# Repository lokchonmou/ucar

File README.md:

# ucar
ucar is a Arduino Nano base, PCB integrate,  universal purpose robot car 
This repository include PCB eagle circuit and an I2C LCD user interface firmware for line following

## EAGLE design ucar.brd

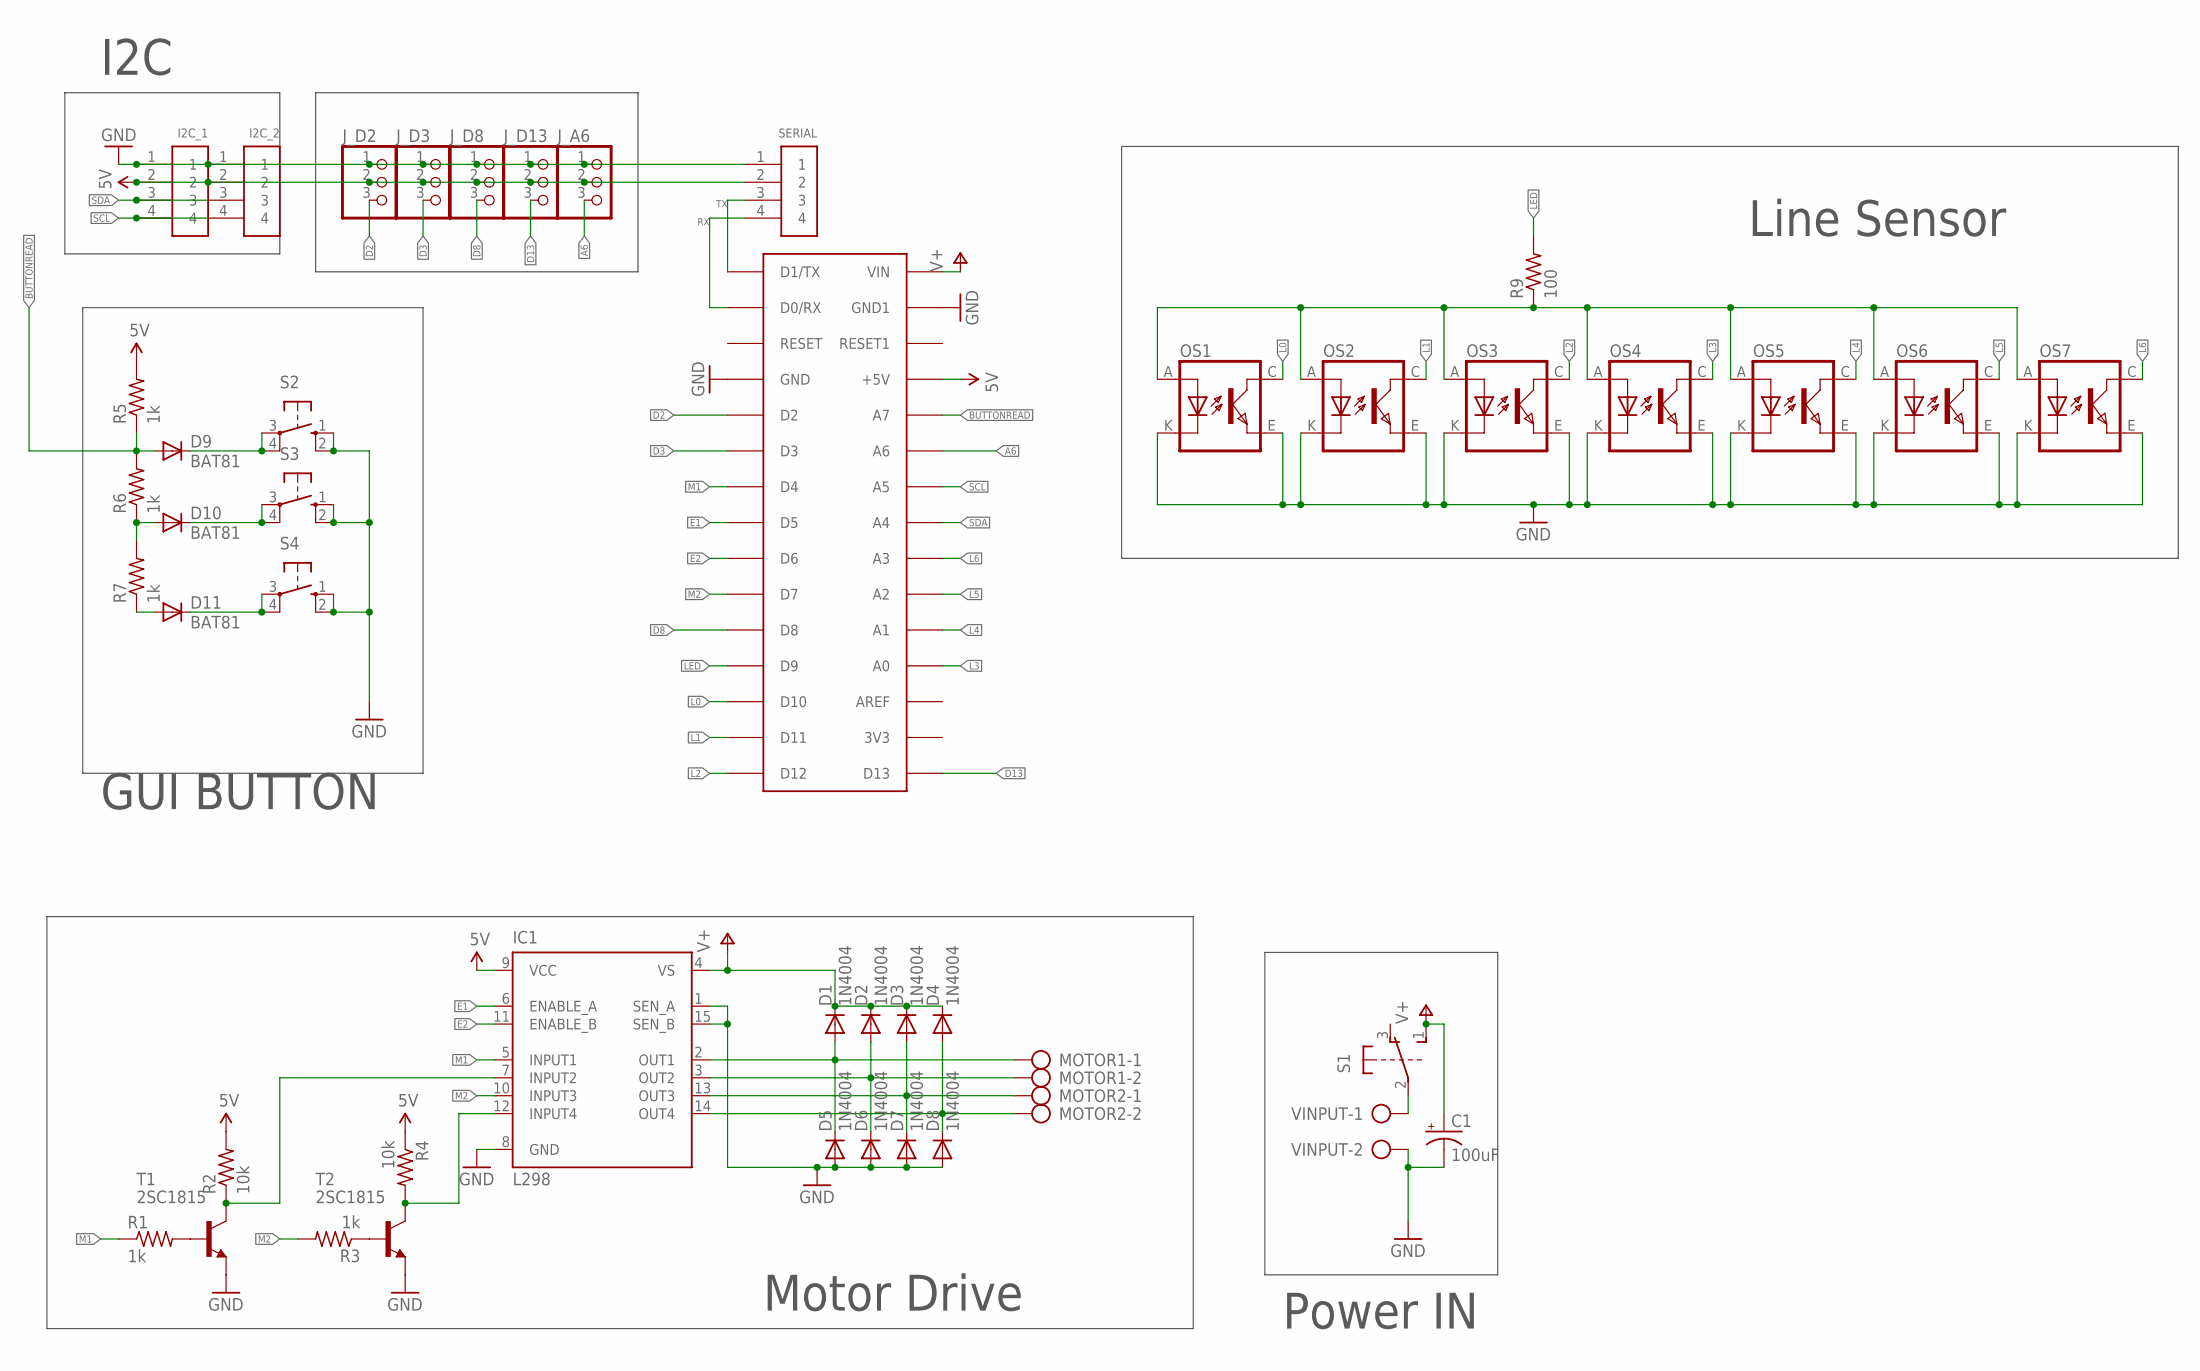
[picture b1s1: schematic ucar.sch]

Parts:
C1: 100uF; E2,5-6
D1, D2, D3, D4, D5, D6, D7, D8: 1N4004; DO41-10
D9, D10, D11: BAT81; DO34-7
I2C_1, I2C_2: 1X4-BIG; 1X04-BIG
IC1: L298; MULTIWATT-15
J_A6: PINHD-1X3; 1X03
J_D2, J_D3, J_D8, J_D13: PINHD-1X3; 1X03
MOTOR1, MOTOR2: AK500/2
OS1, OS2, OS3, OS4, OS5, OS6, OS7: TCRT5000
R1, R3, R5, R6, R7: 1k; 0207/7
R2, R4: 10k; 0207/7
R9: 100; 0204/5
S1: 9077-2
S2, S3, S4: 10-XX; B3F-10XX
SERIAL: 1X4-BIG; 1X04-BIG
T1, T2: 2SC1815; TO92-ECB
U$1: ARDUINONANO; PDIP-32
VINPUT: AK500/2

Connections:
5V: I2C_1.2, I2C_2.2, IC1.9 (VCC), J_A6.2, J_D2.2, J_D3.2, J_D8.2, J_D13.2, R2.2, R4.1, R5.2, SERIAL.2, U$1.+5V
A6: J_A6.3, U$1.A6
BUTTONREAD: D9.A, R5.1, R6.2, U$1.A7
D2: J_D2.3, U$1.D2
D3: J_D3.3, U$1.D3
D8: J_D8.3, U$1.D8
D13: J_D13.3, U$1.D13
E1: IC1.6 (ENABLE_A), U$1.D5
E2: IC1.11 (ENABLE_B), U$1.D6
GND: C1.-, D5.A, D6.A, D7.A, D8.A, I2C_1.1, I2C_2.1, IC1.1 (SEN_A), IC1.8 (GND), IC1.15 (SEN_B), J_A6.1, J_D2.1, J_D3.1, J_D8.1, J_D13.1, OS1.E (EMITTER), OS1.K (CATHODE), OS2.E (EMITTER), OS2.K (CATHODE), OS3.E (EMITTER), OS3.K (CATHODE), OS4.E (EMITTER), OS4.K (CATHODE), OS5.E (EMITTER), OS5.K (CATHODE), OS6.E (EMITTER), OS6.K (CATHODE), OS7.E (EMITTER), OS7.K (CATHODE), S2.1 (S), S2.2 (S1), S3.1 (S), S3.2 (S1), S4.1 (S), S4.2 (S1), SERIAL.1, T1.E, T2.E, U$1.GND, U$1.GND1, VINPUT.2
L0: OS1.C (COLLECTOR), U$1.D10
L1: OS2.C (COLLECTOR), U$1.D11
L2: OS3.C (COLLECTOR), U$1.D12
L3: OS4.C (COLLECTOR), U$1.A0
L4: OS5.C (COLLECTOR), U$1.A1
L5: OS6.C (COLLECTOR), U$1.A2
L6: OS7.C (COLLECTOR), U$1.A3
LED: R9.2, U$1.D9
M1: IC1.5 (INPUT1), R1.1, U$1.D4
M2: IC1.10 (INPUT3), R3.2, U$1.D7
unnamed: OS1.A (ANODE), OS2.A (ANODE), OS3.A (ANODE), OS4.A (ANODE), OS5.A (ANODE), OS6.A (ANODE), OS7.A (ANODE), R9.1
unnamed: R1.2, T1.B
unnamed: D1.A, D5.C, IC1.2 (OUT1), MOTOR1.1
unnamed: R3.1, T2.B
unnamed: D2.A, D6.C, IC1.3 (OUT2), MOTOR1.2
unnamed: D3.A, D7.C, IC1.13 (OUT3), MOTOR2.1
unnamed: IC1.7 (INPUT2), R2.1, T1.C
unnamed: D4.A, D8.C, IC1.14 (OUT4), MOTOR2.2
unnamed: IC1.12 (INPUT4), R4.2, T2.C
unnamed: S1.2, VINPUT.1
unnamed: D10.A, R6.1, R7.2
unnamed: D11.A, R7.1
unnamed: D9.C, S2.3, S2.4 (P1)
unnamed: D10.C, S3.3, S3.4 (P1)
unnamed: D11.C, S4.3, S4.4 (P1)
RX: SERIAL.4, U$1.D0/RX
SCL: I2C_1.4, I2C_2.4, U$1.A5
SDA: I2C_1.3, I2C_2.3, U$1.A4
TX: SERIAL.3, U$1.D1/TX
V+: C1.+, D1.C, D2.C, D3.C, D4.C, IC1.4 (VS), S1.1 (S), U$1.VIN

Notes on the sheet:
Power IN
Motor Drive
I2C
GUI BUTTON
Line Sensor

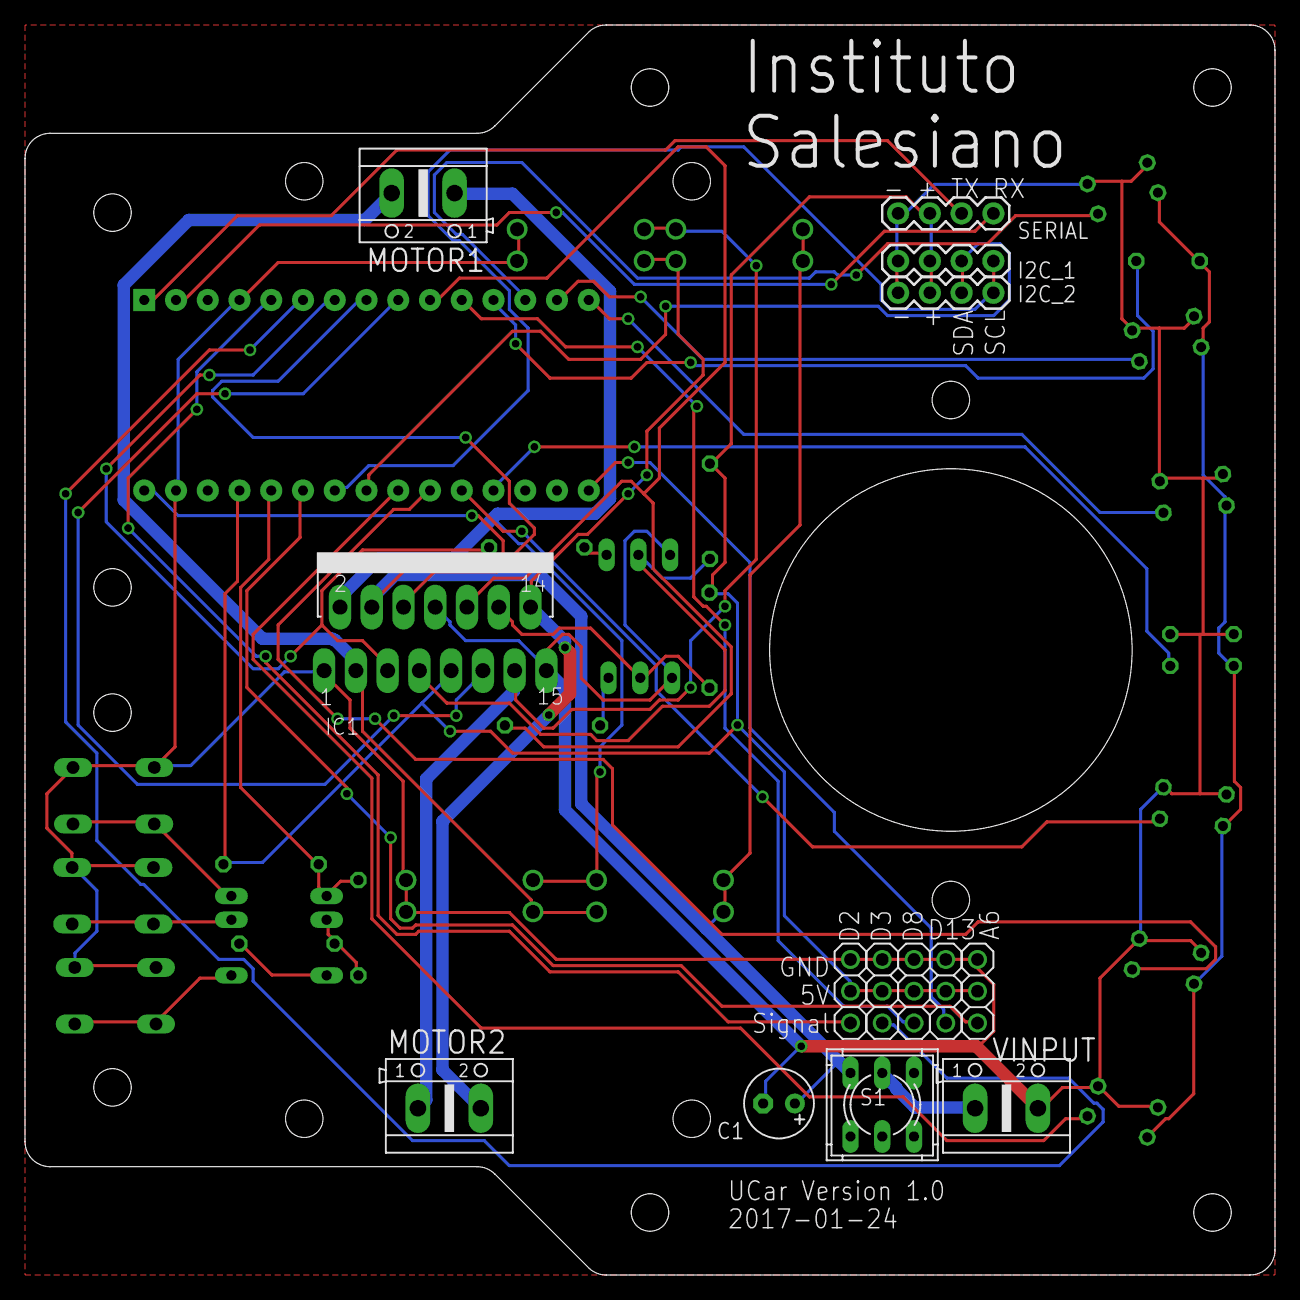
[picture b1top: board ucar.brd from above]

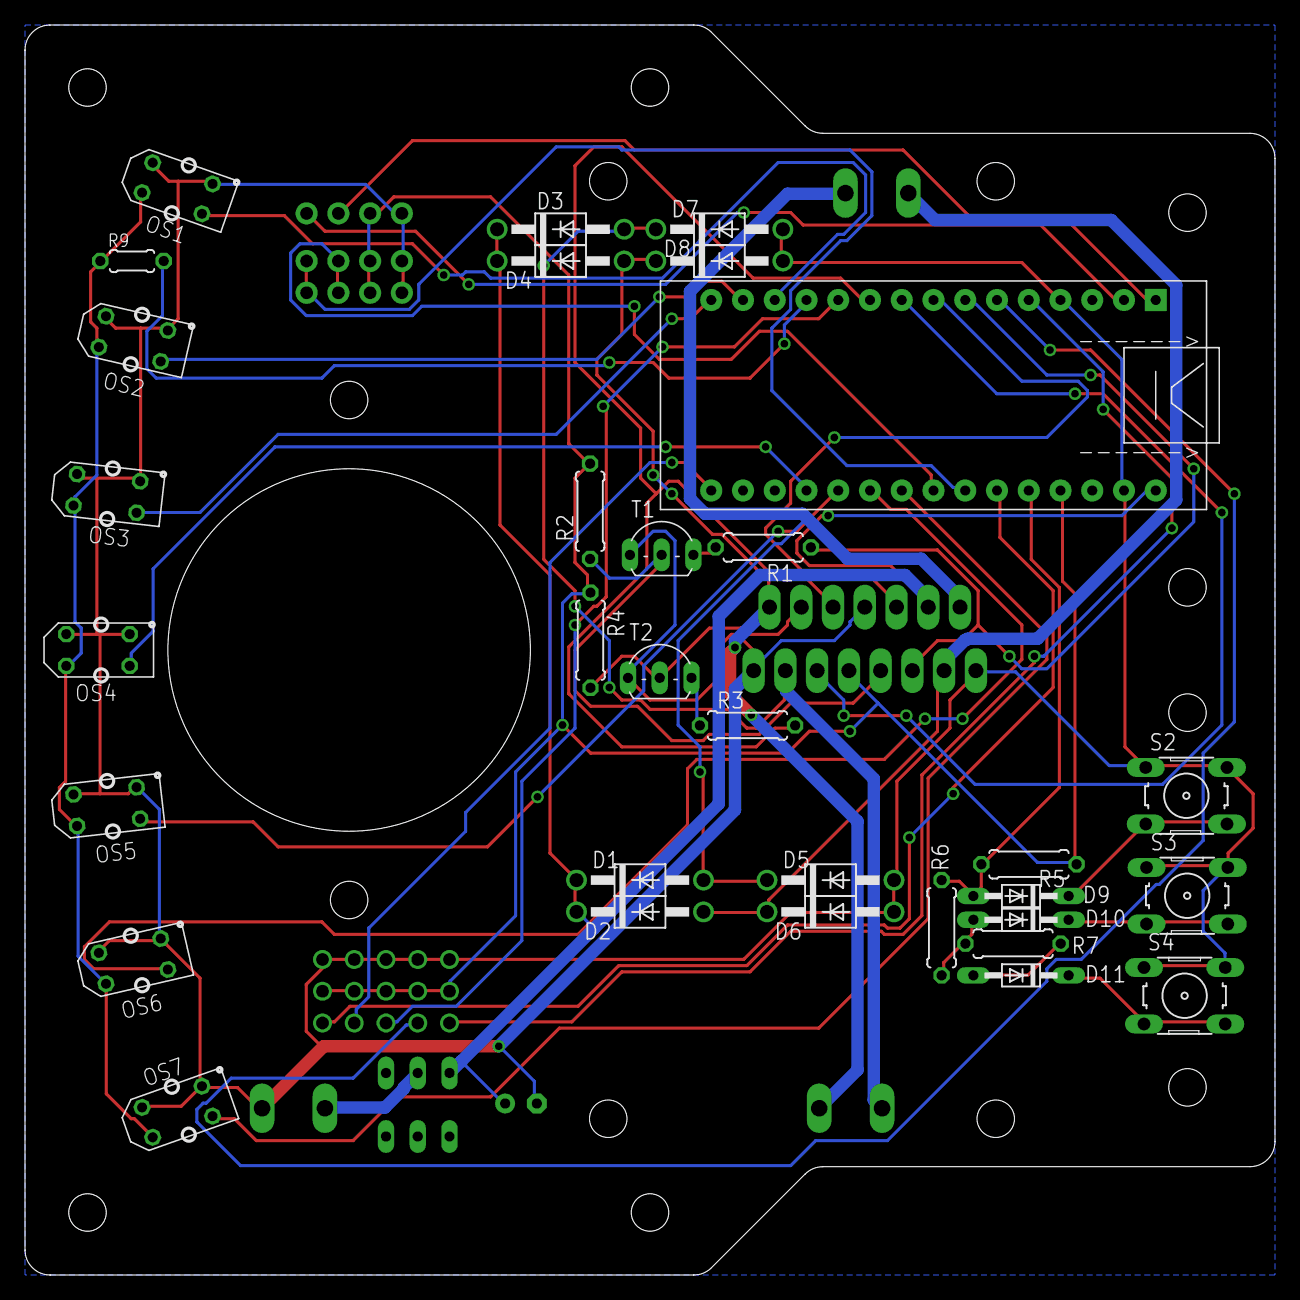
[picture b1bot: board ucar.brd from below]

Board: 2 copper layers, 100.0 x 100.0 mm, 46 parts (32 on the bottom side), 40 nets.

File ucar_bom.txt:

Partlist exported from C:/Users/User/Google ¶³ºÝµwºÐ/Shared/New Elec/Sketch/ucar/tamiya_version/ucar.sch at 2017-01-26 ¬P´Á¥| 14:27

Qty Value       Device        Package      Parts                             Description                          MF MPN      OC_FARNELL OC_NEWARK
3               10-XX         B3F-10XX     S2, S3, S4                        OMRON SWITCH                            B3F-1000 176432     36M3542  
3               AK500/2       AK500/2      MOTOR1, MOTOR2, VINPUT            CONNECTOR                                        unknown    unknown  
5               PINHD-1X3     1X03         J_A6, J_D2, J_D3, J_D8, J_D13     PIN HEADER                                                           
7               TCRT5000      TCRT5000     OS1, OS2, OS3, OS4, OS5, OS6, OS7                                                                      
1   100         R-US_0204/5   0204/5       R9                                RESISTOR, American symbol                                            
1   100uF       CPOL-USE2.5-6 E2,5-6       C1                                POLARIZED CAPACITOR, American symbol                                 
2   10k         R-US_0207/7   0207/7       R2, R4                            RESISTOR, American symbol                                            
8   1N4004      1N4004        DO41-10      D1, D2, D3, D4, D5, D6, D7, D8    DIODE                                                                
3   1X4-BIG     1X4-BIG       1X04-BIG     I2C_1, I2C_2, SERIAL              4-pin connector                                                      
5   1k          R-US_0207/7   0207/7       R1, R3, R5, R6, R7                RESISTOR, American symbol                                            
2   2SC1815     2SC1815       TO92-ECB     T1, T2                            NPN EPITAXIAL TRANSISTOR                                             
1   9077-2      9077-2        9077-2       S1                                MARQUARDT SWITCH 9077.0200                                           
1   ARDUINONANO ARDUINONANO   PDIP-32      U$1                                                                                                    
3   BAT81       BAT81         DO34-7       D9, D10, D11                      DIODE                                                                
1   L298        L298          MULTIWATT-15 IC1                               DUAL FULL-BRIDGE DRIVER                 L298N    1589425    32M1527

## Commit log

2017-01-24 tamiya version
    using Tamiya 70093 gearbox for the car
2017-01-26 version 1.0 修正
    之前忘記加入覆銅，今次補回了，再加上了一個bom

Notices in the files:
parts and their libraries:
SparkFun: Licensing: CC v3.0 Share-Alike You are welcome to use this library for commercial purposes.
